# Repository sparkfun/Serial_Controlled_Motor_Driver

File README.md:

SparkFun Serial Controlled Motor Driver
=======================================

[*SparkFun Serial Controlled Motor Driver (ROB-13911)*](https://www.sparkfun.com/products/13911)

The expandable SparkFun Serial Controlled Motor Driver allows you to control 2 DC motors using a serial command interface over I2C, SPI, or TTL UART. 

Features:
* User port configurable to SPI, I2C, or UART.
* Expansion port utalizing I2C that allows 16 additional drivers
* Auto-enumeration based on connection of expansion 'In' and 'Out' connections - First board becomes first slave in software.
* 1.5 A peak drive per channel
* Bridging mode for any one board to double current drive.
* Operates from 3 to 11 volts with 12v absolute max.
* Stock 3.3v operation of cpu and signals, with VCC breakable to allow up to 5.5v levels.

Repository Contents
-------------------
* **/Documentation** - Datasheet, test information, and diagrams
* **/Firmware** - PSoC projects of embedded firmware
* **/Hardware** - Eagle design files (.brd, .sch)
* **/Libraries** - Libraries for use with the motor driver
* **/Production** - Production files
* **/Software** - Arduino sketches and examples

Documentation
--------------
* **[Library](https://github.com/sparkfun/SparkFun_Serial_Controlled_Motor_Driver_Arduino_Library)** - Arduino library
* **[Hookup Guide](https://learn.sparkfun.com/tutorials/serial-controlled-motor-driver-hookup-guide)** - Basic hookup guide
* **[SparkFun Fritzing repo](https://github.com/sparkfun/Fritzing_Parts)** - Fritzing diagrams for SparkFun products.
* **[SparkFun 3D Model repo](https://github.com/sparkfun/3D_Models)** - 3D models of SparkFun products. 
* **[SparkFun Graphical Datasheets](https://github.com/sparkfun/Graphical_Datasheets)** -Graphical Datasheets for various SparkFun products.

Hardware Compatibility
----------------
* [ROB-13911](https://www.sparkfun.com/products/13911) - Serial controlled motor driver.
* [DEV-14213](https://www.sparkfun.com/products/14213) - SparkFun moto:bit (SCMD_FID_V07a.HEX).

Version History
---------------
* [HW_1.2_FW_1.2](https://github.com/sparkfun/Serial_Controlled_Motor_Driver/tree/HW_1.2_FW_1.2) - Original product
* [V_1.5](https://github.com/sparkfun/Serial_Controlled_Motor_Driver/tree/V_1.5) - Revision prototype 1
* [V_1.6](https://github.com/sparkfun/Serial_Controlled_Motor_Driver/tree/V_1.6) - Revision prototype 2
* [V_1.6.1](https://github.com/sparkfun/Serial_Controlled_Motor_Driver/tree/V_1.6.1) - Revision prototype 2 with non-zero width poly outlines and dev board version V_1.X
* [V_2.0](https://github.com/sparkfun/Serial_Controlled_Motor_Driver/tree/V_2.0) - Version 2.0 of product
* [V_2.0.1](https://github.com/sparkfun/Serial_Controlled_Motor_Driver/tree/V_2.0.1) - Compatible with moto:bit hardware.

License Information
-------------------

This product is _**open source**_! 

Please review the LICENSE.md file for license information. 

If you have any questions or concerns on licensing, please contact techsupport@sparkfun.com.

Distributed as-is; no warranty is given.

- Your friends at SparkFun.

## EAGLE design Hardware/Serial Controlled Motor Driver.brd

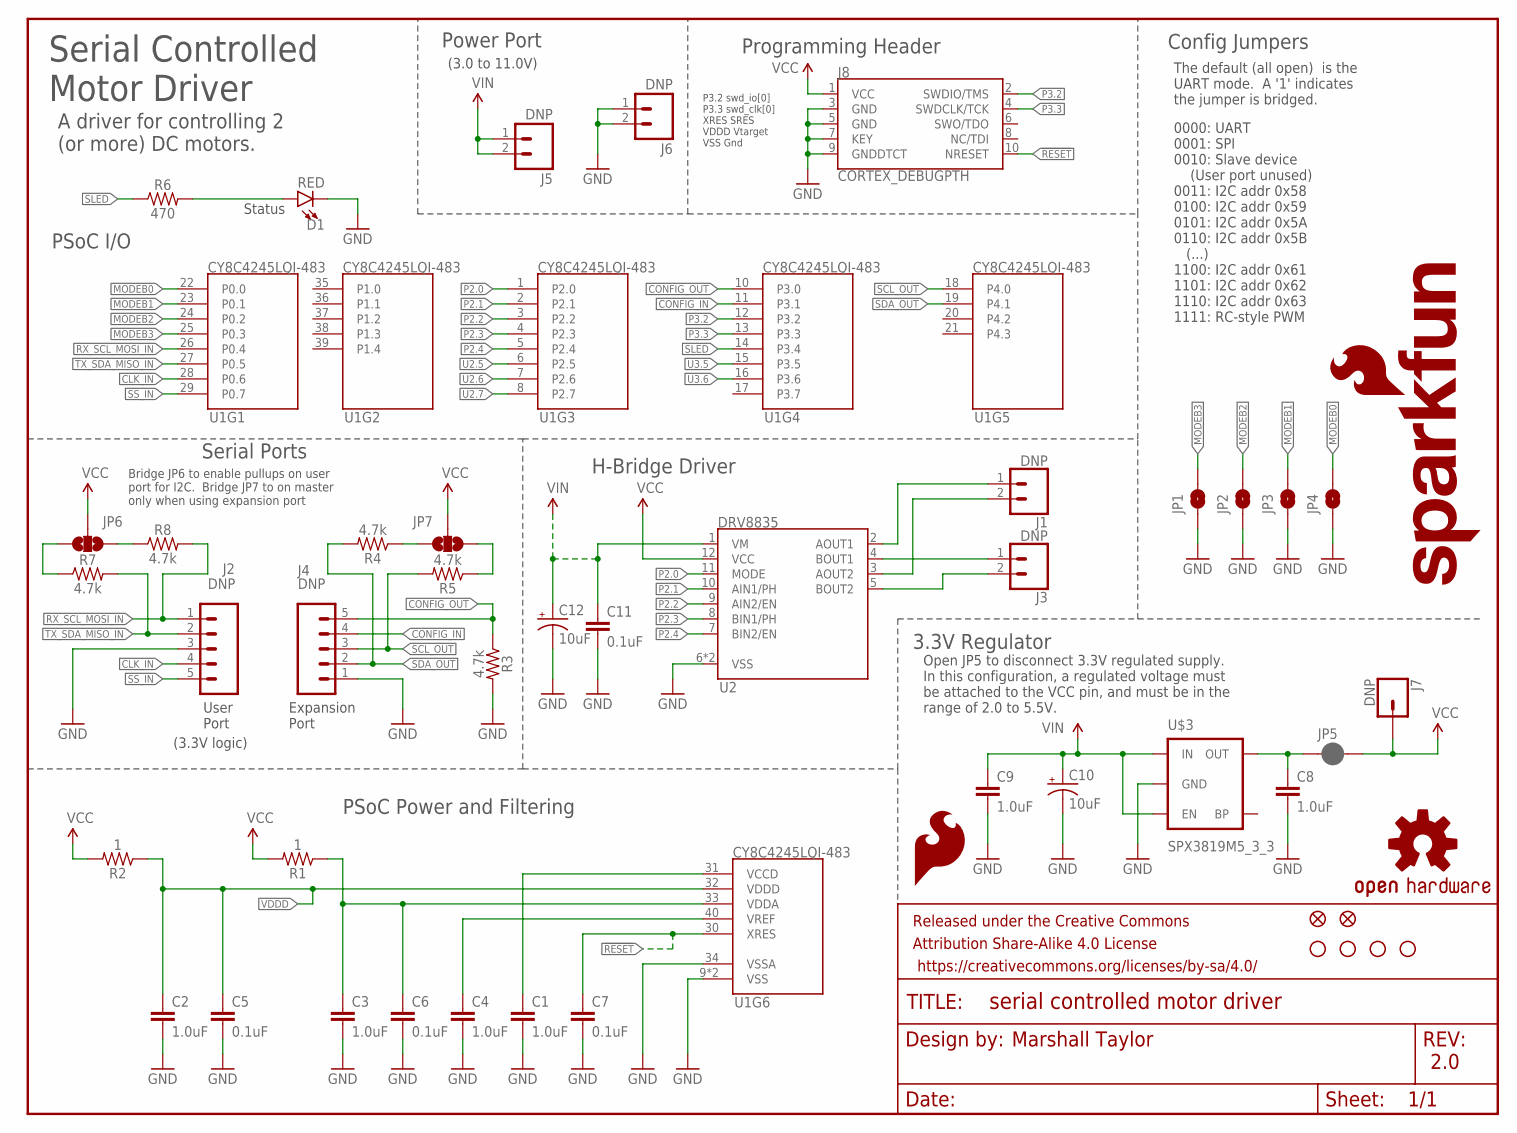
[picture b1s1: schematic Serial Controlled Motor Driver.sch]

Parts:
C1, C2, C3, C4, C8, C9: 1.0uF; 0402
C5, C6, C7, C11: 0.1uF; 0402
C10, C12: 10uF; EIA3216
D1: RED; LED-0603
FD1, FD2: FIDUCIALUFIDUCIAL; MICRO-FIDUCIAL
FRAME1: FRAME-LETTER; CREATIVE_COMMONS
H1, H2, H3, H4: STAND-OFF
J1, J3: DNP; 1X02_NO_SILK
J2, J4: DNP; 1X05
J5, J6: DNP; 1X02@1
J7: DNP; 1X01
J8: CORTEX_DEBUGPTH; 2X5-PTH-1.27MM
JP1, JP2, JP3, JP4: JUMPER-PAD-2; PAD-JUMPER-2-NO_YES_SILK
JP5: JUMPER-PAD-2; PAD-JUMPER-2-NC_BY_PASTE_YES_SILK
JP6, JP7: JUMPER-PAD-3-NOYES_SILK; PAD-JUMPER-3-NO_YES_SILK
LOGO1: SFE_LOGO_FLAME.1_INCH; SFE_LOGO_FLAME_.1
LOGO2: OSHW-LOGOMINI; OSHW-LOGO-MINI
LOGO3: SFE_LOGO_NAME_FLAME.1_INCH; SFE_LOGO_NAME_FLAME_.1
R1, R2: 1; 0603
R3, R4, R5, R7, R8: 4.7k; 0603
R6: 470; 0603
U1: CY8C4245LQI-483; QFN-40
U2: DRV8835; WSON-12
U$3: SPX3819M5_3_3; SOT-23-5-VREG

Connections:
!RESET: C7.1, J8.10 (NRESET), U1.30 (XRES)
AOUT1: J1.1, U2.2 (AOUT1)
AOUT2: J1.2, U2.3 (AOUT2)
BOUT1: J3.1, U2.4 (BOUT1)
BOUT2: J3.2, U2.5 (BOUT2)
CLK_IN: J2.4, U1.28 (P0.6)
CONFIG_IN: J4.4, U1.11 (P3.1)
CONFIG_OUT: J4.5, R3.1, U1.10 (P3.0)
GND: C1.2, C2.2, C3.2, C4.2, C5.2, C6.2, C7.2, C8.2, C9.2, C10.-, C11.2, C12.-, D1.C, J2.3, J4.1, J6.1, J6.2, J8.3 (GND), J8.5 (GND), J8.7 (KEY), J8.9 (GNDDTCT), JP1.1, JP2.1, JP3.1, JP4.1, R3.2, U1.9 (VSS), U1.34 (VSSA), U1.EP (VSS), U2.6 (VSS), U2.PAD (VSS), U$3.2 (GND)
MODEB0: JP4.2, U1.22 (P0.0)
MODEB1: JP3.2, U1.23 (P0.1)
MODEB2: JP2.2, U1.24 (P0.2)
MODEB3: JP1.2, U1.25 (P0.3)
unnamed: C1.1, U1.31 (VCCD)
unnamed: JP7.1, R4.1
unnamed: C3.1, C6.1, R1.1, U1.33 (VDDA)
unnamed: C4.1, U1.40 (VREF)
unnamed: C8.1, JP5.1, U$3.5 (OUT)
unnamed: JP7.3, R5.1
unnamed: D1.A, R6.2
unnamed: JP6.1, R8.1
unnamed: JP6.3, R7.1
P2.0: U1.1 (P2.0), U2.11 (MODE)
P2.1: U1.2 (P2.1), U2.10 (AIN1/PH)
P2.2: U1.3 (P2.2), U2.9 (AIN2/EN)
P2.3: U1.4 (P2.3), U2.8 (BIN1/PH)
P2.4: U1.5 (P2.4), U2.7 (BIN2/EN)
P3.2: J8.2 (SWDIO/TMS), U1.12 (P3.2)
P3.3: J8.4 (SWDCLK/TCK), U1.13 (P3.3)
RX_SCL_MOSI_IN: J2.1, R8.2, U1.26 (P0.4)
SCL_OUT: J4.3, R5.2, U1.18 (P4.0)
SDA_OUT: J4.2, R4.2, U1.19 (P4.1)
SLED: R6.1, U1.14 (P3.4)
SS_IN: J2.5, U1.29 (P0.7)
TX_SDA_MISO_IN: J2.2, R7.2, U1.27 (P0.5)
U2.5: U1.6 (P2.5)
U2.6: U1.7 (P2.6)
U2.7: U1.8 (P2.7)
U3.5: U1.15 (P3.5)
U3.6: U1.16 (P3.6)
VCC: J7.1, J8.1 (VCC), JP5.2, JP6.2, JP7.2, R1.2, R2.2, U2.12 (VCC)
VDDD: C2.1, C5.1, R2.1, U1.32 (VDDD)
VIN: C9.1, C10.+, C11.1, C12.+, J5.1, J5.2, U2.1 (VM), U$3.1 (IN), U$3.3 (EN)

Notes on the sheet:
PSoC Power and Filtering
Serial Controlled Motor Driver
Config Jumpers
Marshall Taylor
PSoC I/O
3.3V Regulator
2.0
P3.2 swd_io[0] P3.3 swd_clk[0] XRES SRES VDDD Vtarget VSS Gnd
Serial Ports
Power Port
Programming Header
H-Bridge Driver
A driver for controlling 2 (or more) DC motors.
0000: UART 0001: SPI 0010: Slave device (User port unused) 0011: I2C addr 0x58 0100: I2C addr 0x59 0101: I2C addr 0x5A 0110: I2C addr 0x5B (...) 1100: I2C addr 0x61 1101: I2C addr 0x62 1110: I2C addr 0x63 1111: RC-style PWM
The default (all open) is the UART mode. A '1' indicates the jumper is bridged.
Status
(3.0 to 11.0V)
Expansion Port
User Port
Open JP5 to disconnect 3.3V regulated supply. In this configuration, a regulated voltage must be attached to the VCC pin, and must be in the range of 2.0 to 5.5V.
Bridge JP6 to enable pullups on user port for I2C. Bridge JP7 to on master only when using expansion port
(3.3V logic)

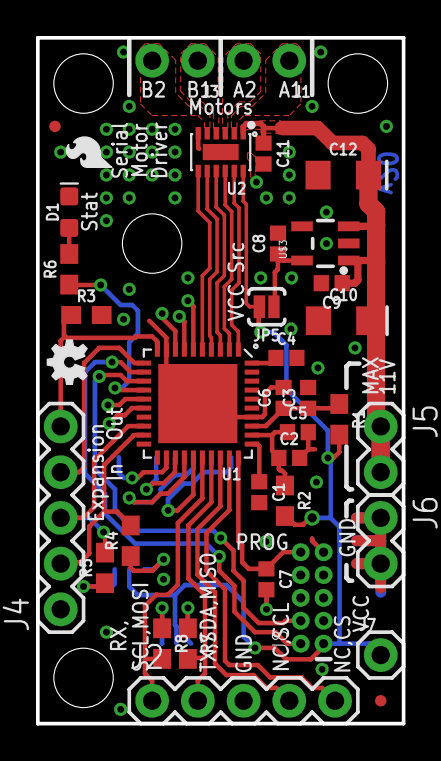
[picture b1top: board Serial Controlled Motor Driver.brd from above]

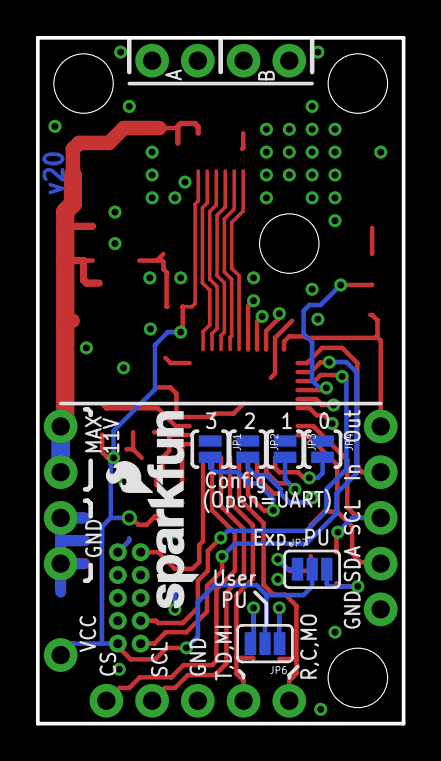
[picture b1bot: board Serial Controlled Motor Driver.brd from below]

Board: 2 copper layers, 20.3 x 38.1 mm, 49 parts (7 on the bottom side), 38 nets.

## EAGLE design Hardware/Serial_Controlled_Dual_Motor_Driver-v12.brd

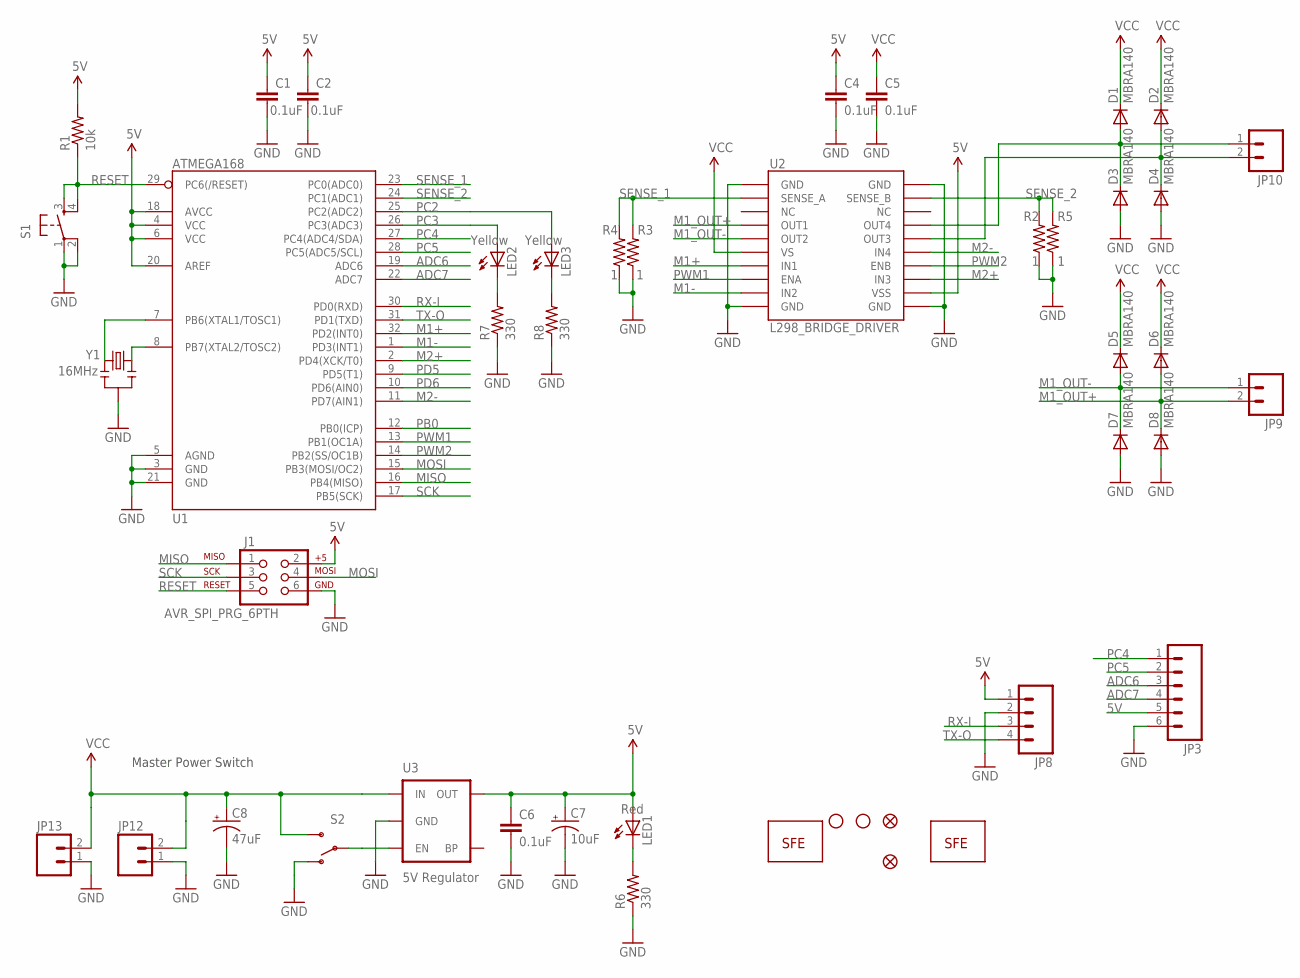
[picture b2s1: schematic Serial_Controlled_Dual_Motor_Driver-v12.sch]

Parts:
C1, C2, C4, C5, C6: 0.1uF; 0603-CAP
C7: 10uF; EIA3216
C8: 47uF; EIA3528
D1, D2, D3, D4, D5, D6, D7, D8: MBRA140; SMA-DIODE
J1: AVR_SPI_PRG_6PTH; 2X3
JP1: LOGO-SFENEW; SFE-NEW-WEBLOGO
JP2, JP6: STAND-OFF
JP3: M06SIP; 1X06
JP4, JP5: FIDUCIAL1X2; FIDUCIAL-1X2
JP7: LOGO-SFESK; SFE-LOGO-FLAME
JP8: M04PTH; 1X04
JP9, JP10, JP13: M02PTH; 1X02
JP12: M02-JST-2MM-SMT; S2B-PH
LED1: Red; LED-0603
LED2, LED3: Yellow; LED-0603
R1: 10k; 0603-RES
R2, R3, R4, R5: 1; 0603-RES
R6, R7, R8: 330; 0603-RES
S1: TAC_SWITCHSMD; TACTILE_SWITCH_SMD
S2: SWITCH-SPSTSMD; AYZ0202
U1: ATMEGA168; TQFP32-08
U2: L298_BRIDGE_DRIVER; POWERSO20
U3: 5V Regulator; SOT23-5
Y1: 16MHz; RESONATOR-SMD

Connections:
5V: C1.1, C2.1, C4.1, C6.1, C7.A (+), J1.2, JP3.5, JP8.1, LED1.A, R1.2, U1.4 (VCC), U1.6 (VCC), U1.18 (AVCC), U1.20 (AREF), U2.P$12 (VSS), U3.5 (OUT)
ADC6: JP3.3, U1.19 (ADC6)
ADC7: JP3.4, U1.22 (ADC7)
GND: C1.2, C2.2, C4.2, C5.2, C6.2, C7.C (-), C8.C (-), D3.A, D4.A, D7.A, D8.A, J1.6, JP3.6, JP8.2, JP12.1, JP13.1, R2.1, R3.1, R4.1, R5.1, R6.1, R7.1, R8.1, S1.1, S1.2, S2.1 (O), U1.3 (GND), U1.5 (AGND), U1.21 (GND), U2.P$1 (GND), U2.P$10 (GND), U2.P$11 (GND), U2.P$20 (GND), U3.2 (GND), Y1.2
M1+: U1.32 (PD2(INT0)), U2.P$7 (IN1)
M1-: U1.1 (PD3(INT1)), U2.P$9 (IN2)
M1_OUT+: D6.A, D8.C, JP9.2, U2.P$4 (OUT1)
M1_OUT-: D5.A, D7.C, JP9.1, U2.P$5 (OUT2)
M2+: U1.2 (PD4(XCK/T0)), U2.P$13 (IN3)
M2-: U1.11 (PD7(AIN1)), U2.P$15 (IN4)
M2_OUT+: D2.A, D4.C, JP10.2, U2.P$16 (OUT3)
M2_OUT-: D1.A, D3.C, JP10.1, U2.P$17 (OUT4)
MISO: J1.1, U1.16 (PB4(MISO))
MOSI: J1.4, U1.15 (PB3(MOSI/OC2))
unnamed: S2.2, U3.3 (EN)
unnamed: U1.8 (PB7(XTAL2/TOSC2)), Y1.3
unnamed: U1.7 (PB6(XTAL1/TOSC1)), Y1.1
unnamed: LED2.C, R7.2
unnamed: LED3.C, R8.2
unnamed: LED1.C, R6.2
PB0: U1.12 (PB0(ICP))
PC2: LED3.A, U1.25 (PC2(ADC2))
PC3: LED2.A, U1.26 (PC3(ADC3))
PC4: JP3.1, U1.27 (PC4(ADC4/SDA))
PC5: JP3.2, U1.28 (PC5(ADC5/SCL))
PD5: U1.9 (PD5(T1))
PD6: U1.10 (PD6(AIN0))
PWM1: U1.13 (PB1(OC1A)), U2.P$8 (ENA)
PWM2: U1.14 (PB2(SS/OC1B)), U2.P$14 (ENB)
RESET: J1.5, R1.1, S1.3, S1.4, U1.29 (PC6(/RESET))
RX-I: JP8.3, U1.30 (PD0(RXD))
SCK: J1.3, U1.17 (PB5(SCK))
SENSE_1: R3.2, R4.2, U1.23 (PC0(ADC0)), U2.P$2 (SENSE_A)
SENSE_2: R2.2, R5.2, U1.24 (PC1(ADC1)), U2.P$19 (SENSE_B)
TX-O: JP8.4, U1.31 (PD1(TXD))
VCC: C5.1, C8.A (+), D1.C, D2.C, D5.C, D6.C, JP12.2, JP13.2, S2.3 (S), U2.P$6 (VS), U3.1 (IN)

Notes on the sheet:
Master Power Switch

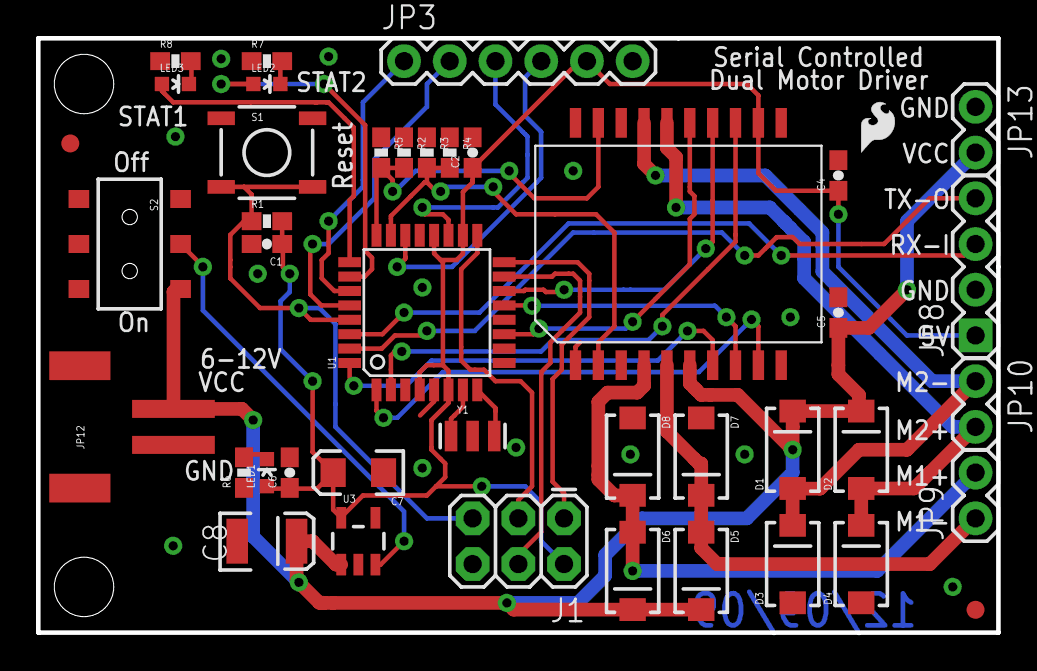
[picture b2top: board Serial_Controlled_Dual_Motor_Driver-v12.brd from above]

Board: 2 copper layers, 53.3 x 33.0 mm, 45 parts (1 on the bottom side), 33 nets.

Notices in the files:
parts and their libraries:
SparkFun-Capacitors: Licensing: Creative Commons ShareAlike 4.0 International - https://creativecommons.org/licenses/by-sa/4.0
SparkFun-Aesthetics: Released under the Creative Commons Attribution Share-Alike 4.0 License
SparkFun-Aesthetics: https://creativecommons.org/licenses/by-sa/4.0
